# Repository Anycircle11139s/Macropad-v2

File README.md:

# Macropad-v2
<br>
<Br>

I wanted to make a second version of my macropad because I was confident, that with my improved skills, I could cook up something better. I spent a long time creating this, and I'm really proud of what I made. I just started by brainstorming what I wanted in my hackpad, and I searched up cool features to add, eventually ending with me designing a macropad and case with these items:
- Joystick
- 2 sliders
- 2 oleds
- buzzer
- Haptics
- rotary encoder
- cool cad case
- 12 switches
- Trackball
- hand gesture sensor
- bluetooth

<BR>
<br>

<BR>
<br>

<br>

<br>

BOM:
<Br>

|Name                |Purpose                               |Quantity|Total Cost (USD)|Link                                                                                                                                                                                                                                                                                                                                                                                                                                                                                                                                                                                                                                                                                                                                                                                   |Distributor|
|--------------------|--------------------------------------|--------|----------------|---------------------------------------------------------------------------------------------------------------------------------------------------------------------------------------------------------------------------------------------------------------------------------------------------------------------------------------------------------------------------------------------------------------------------------------------------------------------------------------------------------------------------------------------------------------------------------------------------------------------------------------------------------------------------------------------------------------------------------------------------------------------------------------|-----------|
|Case                |the case bruh                         |1       |6.50            |                                                                                                                                                                                                                                                                                                                                                                                                                                                                                                                                                                                                                                                                                                                                                                                       |Printing legion|
|PCB                 |the pcb ;(                            |1       |21.00           |                                                                                                                                                                                                                                                                                                                                                                                                                                                                                                                                                                                                                                                                                                                                                                                       |JLCPCB     |
|lipo battery        |battery                               |1       |0.99            |https://www.aliexpress.com/item/1005011541940994.html?spm=a2g0o.productlist.main.1.78703235cGbLFG&algo_pvid=9ee0d42c-760b-4657-89e7-614624b4ca0b&algo_exp_id=9ee0d42c-760b-4657-89e7-614624b4ca0b-0&pdp_ext_f=%7B%22order%22%3A%2291%22%2C%22eval%22%3A%221%22%2C%22fromPage%22%3A%22search%22%7D&pdp_npi=6%40dis%21USD%2113.94%210.99%21%21%2194.86%216.74%21%4021030a6217771838339585944e4a30%2112000055868825938%21sea%21AU%217402515296%21X%211%210%21n_tag%3A-29911%3Bd%3Aef1e07f3%3Bm03_new_user%3A-29895%3BpisId%3A5000000204047332&curPageLogUid=xRO33uo723qw&utparam-url=scene%3Asearch%7Cquery_from%3A%7Cx_object_id%3A1005011541940994%7C_p_origin_prod%3A                                                                                                                  |ali express|
|joystick            |for joy and happiness and sticks      |2       |0.99            |https://www.aliexpress.com/item/1005006375332797.html?spm=a2g0o.productlist.main.15.5f8999mT99mTyR&algo_pvid=a52f8a2f-d575-4ad3-bee8-e1a1bf34a230&algo_exp_id=a52f8a2f-d575-4ad3-bee8-e1a1bf34a230-12&pdp_ext_f=%7B%22order%22%3A%221642%22%2C%22eval%22%3A%221%22%2C%22fromPage%22%3A%22search%22%7D&pdp_npi=6%40dis%21USD%215.56%210.99%21%21%2137.82%216.70%21%40210328db17771815335367219ee95e%2112000037014017250%21sea%21AU%217402515296%21X%211%210%21n_tag%3A-29911%3Bd%3Aef1e07f3%3Bm03_new_user%3A-29895%3BpisId%3A5000000204047332&curPageLogUid=3UEUdfj2OnjF&utparam-url=scene%3Asearch%7Cquery_from%3A%7Cx_object_id%3A1005006375332797%7C_p_origin_prod%3A                                                                                                               |ali express|
|slide pot           |sliders                               |2       |5.70            |https://www.aliexpress.com/item/1005008713345793.html?spm=a2g0o.productlist.main.2.60983Pyu3PyuP1&algo_pvid=b0022195-0b79-4524-aa97-ece731d8ad54&algo_exp_id=b0022195-0b79-4524-aa97-ece731d8ad54-1&pdp_ext_f=%7B%22order%22%3A%22681%22%2C%22eval%22%3A%221%22%2C%22fromPage%22%3A%22search%22%7D&pdp_npi=6%40dis%21USD%212.66%210.99%21%21%2118.09%216.73%21%402101ee6617771813279241737e662c%2112000046545295127%21sea%21AU%217402515296%21X%211%210%21n_tag%3A-29911%3Bd%3Aef1e07f3%3Bm03_new_user%3A-29895%3BpisId%3A5000000204047332&curPageLogUid=FXsnTpFwKMfe&utparam-url=scene%3Asearch%7Cquery_from%3A%7Cx_object_id%3A1005008713345793%7C_p_origin_prod%3A                                                                                                                  |ali express|
|haptic motor        |haptics                               |1       |1.82            |https://www.aliexpress.com/item/1005007159921749.html?spm=a2g0o.productlist.main.28.3a4fJNUzJNUzMS&algo_pvid=4b836aab-1aa2-46ce-8623-293a19b2cf31&algo_exp_id=4b836aab-1aa2-46ce-8623-293a19b2cf31-25&pdp_ext_f=%7B%22order%22%3A%22448%22%2C%22eval%22%3A%221%22%2C%22fromPage%22%3A%22search%22%7D&pdp_npi=6%40dis%21USD%211.79%210.99%21%21%211.79%210.99%21%402101dedf17771845479125689ef0ce%2112000055867640789%21sea%21AU%217402515296%21X%211%210%21n_tag%3A-29911%3Bd%3Aef1e07f3%3Bm03_new_user%3A-29895%3BpisId%3A5000000204047332&curPageLogUid=zrmwNkYZNhYB&utparam-url=scene%3Asearch%7Cquery_from%3A%7Cx_object_id%3A1005007159921749%7C_p_origin_prod%3A                                                                                                                 |ali express|
|trackball           |trackball                             |1       |3.70            |https://www.aliexpress.com/item/1005008126890596.html?src=google#nav-description                                                                                                                                                                                                                                                                                                                                                                                                                                                                                                                                                                                                                                                                                                       |ali express|
|tof sensor          |hand gestures                         |1       |1.54            |https://www.aliexpress.com/item/1005006864257651.html?spm=a2g0o.productlist.main.4.351chWtAhWtATp&aem_p4p_detail=202604242032431273050239645690001515361&algo_pvid=fb4b63c4-da61-480d-ab27-ada5671d1d0b&algo_exp_id=fb4b63c4-da61-480d-ab27-ada5671d1d0b-3&pdp_ext_f=%7B%22order%22%3A%22413%22%2C%22eval%22%3A%221%22%2C%22fromPage%22%3A%22search%22%7D&pdp_npi=6%40dis%21USD%2135.42%211.54%21%21%21240.96%2110.50%21%402103212b17770879639204117eb09f%2112000038554217788%21sea%21AU%217402515296%21X%211%210%21n_tag%3A-29911%3Bd%3Aef1e07f3%3Bm03_new_user%3A-29895%3BpisId%3A5000000204047332&curPageLogUid=MrmJQzMoGh3t&utparam-url=scene%3Asearch%7Cquery_from%3A%7Cx_object_id%3A1005006864257651%7C_p_origin_prod%3A&search_p4p_id=202604242032431273050239645690001515361_1|ali express|
|DRV2605LDGS         |haptics driver                        |1       |3.60            |https://www.aliexpress.com/item/1005009975089617.html?spm=a2g0o.productlist.main.3.40e462b9pzbfZW&algo_pvid=4767538b-1ca2-4c58-b87e-f0fffccde297&algo_exp_id=4767538b-1ca2-4c58-b87e-f0fffccde297-2&pdp_ext_f=%7B%22order%22%3A%2229%22%2C%22eval%22%3A%221%22%2C%22fromPage%22%3A%22search%22%7D&pdp_npi=6%40dis%21USD%214.00%213.60%21%21%214.00%213.60%21%40210328db17770790445696115ee946%2112000050735812690%21sea%21AU%217402515296%21X%211%210%21n_tag%3A-29911%3Bd%3Aef1e07f3%3Bm03_new_user%3A-29895&curPageLogUid=5ZwdNp8fQ9ho&utparam-url=scene%3Asearch%7Cquery_from%3A%7Cx_object_id%3A1005009975089617%7C_p_origin_prod%3A                                                                                                                                               |ali express|
|24LC256             |for extra memory                      |1       |3.67            |https://www.aliexpress.com/item/1005007758875314.html?spm=a2g0o.productlist.main.1.1ba8766eaBLlFp&algo_pvid=40afdb6a-6caa-4c82-9273-4b09ec377997&algo_exp_id=40afdb6a-6caa-4c82-9273-4b09ec377997-0&pdp_ext_f=%7B%22order%22%3A%2272%22%2C%22eval%22%3A%221%22%2C%22fromPage%22%3A%22search%22%7D&pdp_npi=6%40dis%21USD%211.15%211.15%21%21%217.80%217.80%21%402103126e17771071385293001e5951%2112000042106872103%21sea%21AU%217402515296%21X%211%210%21n_tag%3A-29911%3Bd%3Aef1e07f3%3Bm03_new_user%3A-29895&curPageLogUid=d8mRjZi8dGUy&utparam-url=scene%3Asearch%7Cquery_from%3A%7Cx_object_id%3A1005007758875314%7C_p_origin_prod%3A                                                                                                                                               |Ali express|
|I2C channel switcher|so I can run I2C with that many things|1       |2.94            |https://www.aliexpress.com/item/4000321651168.html?spm=a2g0o.productlist.main.4.7c875bbcNb0561&aem_p4p_detail=202604241744053201409699771840001428483&algo_pvid=184a297b-85c3-4432-947e-2ee3c0819f25&algo_exp_id=184a297b-85c3-4432-947e-2ee3c0819f25-3&pdp_ext_f=%7B%22order%22%3A%2256%22%2C%22eval%22%3A%221%22%2C%22fromPage%22%3A%22search%22%7D&pdp_npi=6%40dis%21USD%213.27%212.94%21%21%213.27%212.94%21%402101c59117770778453443477e32c9%2110000001317042990%21sea%21AU%217402515296%21X%211%210%21n_tag%3A-29911%3Bd%3Aef1e07f3%3Bm03_new_user%3A-29895&curPageLogUid=kvqc1Zd7ka2i&utparam-url=scene%3Asearch%7Cquery_from%3A%7Cx_object_id%3A4000321651168%7C_p_origin_prod%3A&search_p4p_id=202604241744053201409699771840001428483_1                                      |ali express|
|ads1115             |for the sliders and joystick          |1       |3.27            |https://www.aliexpress.com/item/4000116831589.html?spm=a2g0o.productlist.main.4.e4367170pqiJeh&algo_pvid=54b18df7-b4a7-4482-b792-d480d9cb0b9a&aem_p4p_detail=202604241740286255615724926120001424947&algo_exp_id=54b18df7-b4a7-4482-b792-d480d9cb0b9a-3&pdp_ext_f=%7B%22order%22%3A%22359%22%2C%22eval%22%3A%221%22%2C%22fromPage%22%3A%22search%22%7D&pdp_npi=6%40dis%21USD%213.63%213.27%21%21%213.63%213.27%21%402101eee917770776282871616e7bde%2112000031353532263%21sea%21AU%217402515296%21X%211%210%21n_tag%3A-29911%3Bd%3Aef1e07f3%3Bm03_new_user%3A-29895&curPageLogUid=sNNybvIUvGwU&utparam-url=scene%3Asearch%7Cquery_from%3A%7Cx_object_id%3A4000116831589%7C_p_origin_prod%3A&search_p4p_id=202604241740286255615724926120001424947_1                                     |ali express|
|io expander         |more pins                             |1       |3.83            |https://www.aliexpress.com/item/1005006123427728.html?spm=a2g0o.productlist.main.4.7a5eTuUZTuUZsd&aem_p4p_detail=202604241737018054978755135470001446003&algo_pvid=2935dea7-c566-4d6d-8b4a-c8921f2ee585&algo_exp_id=2935dea7-c566-4d6d-8b4a-c8921f2ee585-3&pdp_ext_f=%7B%22order%22%3A%2213%22%2C%22eval%22%3A%221%22%2C%22fromPage%22%3A%22search%22%7D&pdp_npi=6%40dis%21USD%213.83%213.83%21%21%2126.05%2126.05%21%4021033d1217770774214177052eb5ec%2112000035859022158%21sea%21AU%217402515296%21X%211%210%21n_tag%3A-29911%3Bd%3Aef1e07f3%3Bm03_new_user%3A-29895&curPageLogUid=0Dl325w86X0G&utparam-url=scene%3Asearch%7Cquery_from%3A%7Cx_object_id%3A1005006123427728%7C_p_origin_prod%3A&search_p4p_id=202604241737018054978755135470001446003_1                              |ali express|
|headers             |headers                               |1       |1.23            |https://www.aliexpress.com/item/1005011980100152.html?spm=a2g0o.productlist.main.1.781emfhzmfhz9d&algo_pvid=7a2bb4b6-e92c-4a5b-a89d-71b8a1096902&algo_exp_id=7a2bb4b6-e92c-4a5b-a89d-71b8a1096902-0&pdp_ext_f=%7B%22order%22%3A%2218%22%2C%22eval%22%3A%221%22%2C%22fromPage%22%3A%22search%22%7D&pdp_npi=6%40dis%21USD%211.23%211.20%21%21%211.23%211.20%21%40210328d417770772722275687ecccc%2112000057423435803%21sea%21AU%217402515296%21X%211%210%21n_tag%3A-29911%3Bd%3Aef1e07f3%3Bm03_new_user%3A-29895&curPageLogUid=sG8mgvOClCPu&utparam-url=scene%3Asearch%7Cquery_from%3A%7Cx_object_id%3A1005011980100152%7C_p_origin_prod%3A                                                                                                                                               |ali express|
|buzzer              |buzzing                               |2       |5.50            |https://www.aliexpress.com/item/1005007760117171.html?spm=a2g0o.productlist.main.3.6030mV5emV5e3L&algo_pvid=eef0c9b7-e91c-4ed5-b4f4-4c7a828aafc4&algo_exp_id=eef0c9b7-e91c-4ed5-b4f4-4c7a828aafc4-2&pdp_ext_f=%7B%22order%22%3A%2249%22%2C%22eval%22%3A%221%22%2C%22fromPage%22%3A%22search%22%7D&pdp_npi=6%40dis%21USD%212.87%210.99%21%21%2119.49%216.70%21%402103129f17771804952892675e59d3%2112000042136775304%21sea%21AU%217402515296%21X%211%210%21n_tag%3A-29911%3Bd%3Aef1e07f3%3Bm03_new_user%3A-29895%3BpisId%3A5000000204047332&curPageLogUid=3fwWn3qz4T5N&utparam-url=scene%3Asearch%7Cquery_from%3A%7Cx_object_id%3A1005007760117171%7C_p_origin_prod%3A                                                                                                                   |ali express|
|rotary encoder      |to rotary encode                      |1       |1.29            |https://www.aliexpress.com/item/1005007644083514.html?spm=a2g0o.productlist.main.1.7b187465T0x8DI&algo_pvid=dd42beb6-a89c-4e9a-822a-aee0d3bb8655&algo_exp_id=dd42beb6-a89c-4e9a-822a-aee0d3bb8655-0&pdp_ext_f=%7B%22order%22%3A%222833%22%2C%22spu_best_type%22%3A%22price%22%2C%22eval%22%3A%221%22%2C%22fromPage%22%3A%22search%22%7D&pdp_npi=6%40dis%21USD%211.17%210.99%21%21%211.17%210.99%21%402101ee6617770766332183942e6637%2112000041630839415%21sea%21AU%217402515296%21X%211%210%21n_tag%3A-29911%3Bd%3Aef1e07f3%3Bm03_new_user%3A-29895%3BpisId%3A5000000204047332&curPageLogUid=TOJyxlb254yR&utparam-url=scene%3Asearch%7Cquery_from%3A%7Cx_object_id%3A1005007644083514%7C_p_origin_prod%3A                                                                              |ali express|
|150r resistors      |resisting                             |1       |1.79            |https://www.aliexpress.com/item/1005011779163101.html?spm=a2g0o.productlist.main.1.165bKPGbKPGb9c&algo_pvid=6a77e362-f1ba-4f46-bcf4-28d82e9b39d5&algo_exp_id=6a77e362-f1ba-4f46-bcf4-28d82e9b39d5-0&pdp_ext_f=%7B%22order%22%3A%22384%22%2C%22eval%22%3A%221%22%2C%22fromPage%22%3A%22search%22%7D&pdp_npi=6%40dis%21USD%211.74%211.74%21%21%2111.86%2111.86%21%4021030a4b17770764663682662e7f12%2112000056534710403%21sea%21AU%217402515296%21X%211%210%21n_tag%3A-29911%3Bd%3Aef1e07f3%3Bm03_new_user%3A-29895&curPageLogUid=lPvCdQ65XX0q&utparam-url=scene%3Asearch%7Cquery_from%3A%7Cx_object_id%3A1005011779163101%7C_p_origin_prod%3A                                                                                                                                            |ali express|
|100r resistors      |resisting                             |1       |1.79            |https://www.aliexpress.com/item/1005011779163101.html?spm=a2g0o.productlist.main.1.165bKPGbKPGb9c&algo_pvid=6a77e362-f1ba-4f46-bcf4-28d82e9b39d5&algo_exp_id=6a77e362-f1ba-4f46-bcf4-28d82e9b39d5-0&pdp_ext_f=%7B%22order%22%3A%22384%22%2C%22eval%22%3A%221%22%2C%22fromPage%22%3A%22search%22%7D&pdp_npi=6%40dis%21USD%211.74%211.74%21%21%2111.86%2111.86%21%4021030a4b17770764663682662e7f12%2112000056534710403%21sea%21AU%217402515296%21X%211%210%21n_tag%3A-29911%3Bd%3Aef1e07f3%3Bm03_new_user%3A-29895&curPageLogUid=lPvCdQ65XX0q&utparam-url=scene%3Asearch%7Cquery_from%3A%7Cx_object_id%3A1005011779163101%7C_p_origin_prod%3A                                                                                                                                            |ali express|
|2.2k resistors      |resisting                             |1       |1.79            |https://www.aliexpress.com/item/1005011779163101.html?spm=a2g0o.productlist.main.1.165bKPGbKPGb9c&algo_pvid=6a77e362-f1ba-4f46-bcf4-28d82e9b39d5&algo_exp_id=6a77e362-f1ba-4f46-bcf4-28d82e9b39d5-0&pdp_ext_f=%7B%22order%22%3A%22384%22%2C%22eval%22%3A%221%22%2C%22fromPage%22%3A%22search%22%7D&pdp_npi=6%40dis%21USD%211.74%211.74%21%21%2111.86%2111.86%21%4021030a4b17770764663682662e7f12%2112000056534710403%21sea%21AU%217402515296%21X%211%210%21n_tag%3A-29911%3Bd%3Aef1e07f3%3Bm03_new_user%3A-29895&curPageLogUid=lPvCdQ65XX0q&utparam-url=scene%3Asearch%7Cquery_from%3A%7Cx_object_id%3A1005011779163101%7C_p_origin_prod%3A                                                                                                                                            |ali exress |
|m4 screws           |to mount PCB                          |1       |1.31            |https://www.aliexpress.com/item/1005005879037174.html?mp=1&pdp_npi=6@dis!USD!USD+1.11!USD+1.09!!USD+1.09!!!@2101e2b417770758950625236e1519!12000034679037238!ct!AU!7402515296!!1!0!                                                                                                                                                                                                                                                                                                                                                                                                                                                                                                                                                                                                    |ali express|
|m2 screws           |to hold case together                 |1       |1.58            |https://www.aliexpress.com/item/1005005879037174.html?mp=1&pdp_npi=6@dis!USD!USD+1.11!USD+1.09!!USD+1.09!!!@2101e2b417770758950625236e1519!12000034679037238!ct!AU!7402515296!!1!0!                                                                                                                                                                                                                                                                                                                                                                                                                                                                                                                                                                                                    |ali express|
|Keycaps             |to cover switches                     |1       |4.20            |https://www.aliexpress.com/item/1005008678389468.html?mp=1&pdp_npi=6@dis!USD!USD+4.23!USD+4.23!!USD+4.23!!!@2101e2b417770757558731632e1519!12000046204757642!ct!AU!7402515296!!1!0!                                                                                                                                                                                                                                                                                                                                                                                                                                                                                                                                                                                                    |ali express|
|Diodes              |for switch matrix                     |1       |2.83            |https://www.aliexpress.com/item/1005007606166130.html?mp=1&pdp_npi=6@dis!USD!USD+2.83!USD+2.83!!USD+2.74!!!@2101e2b417770757117688866e1519!12000045210201538!ct!AU!7402515296!!1!0!                                                                                                                                                                                                                                                                                                                                                                                                                                                                                                                                                                                                    |Ali express|
|Oleds               |2 oleds                               |2       |7.00            |https://www.aliexpress.com/item/1005006636072295.html?mp=1&pdp_npi=6@dis!USD!USD+3.50!USD+2.30!!USD+2.28!!!@2101e2b417770756812038247e1519!12000037978554141!ct!AU!7402515296!!1!0!                                                                                                                                                                                                                                                                                                                                                                                                                                                                                                                                                                                                    |ali express|
|Switches            |buttons                               |1       |8.40            |https://www.aliexpress.com/item/1005006425450443.html?mp=1&pdp_npi=6@dis!USD!USD+8.40!USD+0.99!!USD+0.99!!!@2101e2b417770755354165492e1519!12000037120671470!ct!AU!7402515296!!1!0!                                                                                                                                                                                                                                                                                                                                                                                                                                                                                                                                                                                                    |ali express|
|rgb leds            |backlighting                          |1       |3.23            |https://www.aliexpress.com/item/1005005340818659.html?mp=1&pdp_npi=6@dis!USD!USD+3.80!USD+3.23!!USD+3.23!!!@2101e2b417770753745202285e1519!12000032670306832!ct!AU!7402515296!!1!0!                                                                                                                                                                                                                                                                                                                                                                                                                                                                                                                                                                                                    |Ali express|
|Capacitors          |to capacitate                         |1       |1.00            |https://www.aliexpress.com/item/1005010764953411.html?spm=a2g0o.productlist.main.1.e6475d075FSaEj&algo_pvid=772381fe-7654-43a5-9bd3-7f88d16dd3aa&algo_exp_id=772381fe-7654-43a5-9bd3-7f88d16dd3aa-0&pdp_ext_f=%7B%22order%22%3A%22160%22%2C%22eval%22%3A%221%22%2C%22fromPage%22%3A%22search%22%7D&pdp_npi=6%40dis%21USD%216.40%210.99%21%21%2143.56%216.76%21%40210319b717770753721454899e46bd%2112000053431436229%21sea%21AU%217402515296%21X%211%210%21n_tag%3A-29911%3Bd%3Aef1e07f3%3Bm03_new_user%3A-29895%3BpisId%3A5000000204047332&curPageLogUid=IRwD1Amro2MH&utparam-url=scene%3Asearch%7Cquery_from%3A%7Cx_object_id%3A1005010764953411%7C_p_origin_prod%3A                                                                                                                  |ali express|
|Xiao esp32 s3       |microcontroller                       |1       |11.00           |https://www.aliexpress.com/item/1005007870593864.html?spm=a2g0o.productlist.main.2.429f1518C9k5jO&algo_pvid=f75b72cf-3b9b-4d39-bf3e-6999bac9bbf1&algo_exp_id=f75b72cf-3b9b-4d39-bf3e-6999bac9bbf1-1&pdp_ext_f=%7B%22order%22%3A%2285%22%2C%22eval%22%3A%221%22%2C%22fromPage%22%3A%22search%22%7D&pdp_npi=6%40dis%21USD%210.26%210.19%21%21%210.26%210.19%21%4021030a6217771807664662117e4a39%2112000053238173498%21sea%21AU%217402515296%21X%211%210%21n_tag%3A-29911%3Bd%3Aef1e07f3%3Bm03_new_user%3A-29895&curPageLogUid=QZZSsXEuP658&utparam-url=scene%3Asearch%7Cquery_from%3A%7Cx_object_id%3A1005007870593864%7C_p_origin_prod%3A                                                                                                                                               |ali express|
|Total       |                       |113.50       |          |                                                                                                                                             ||

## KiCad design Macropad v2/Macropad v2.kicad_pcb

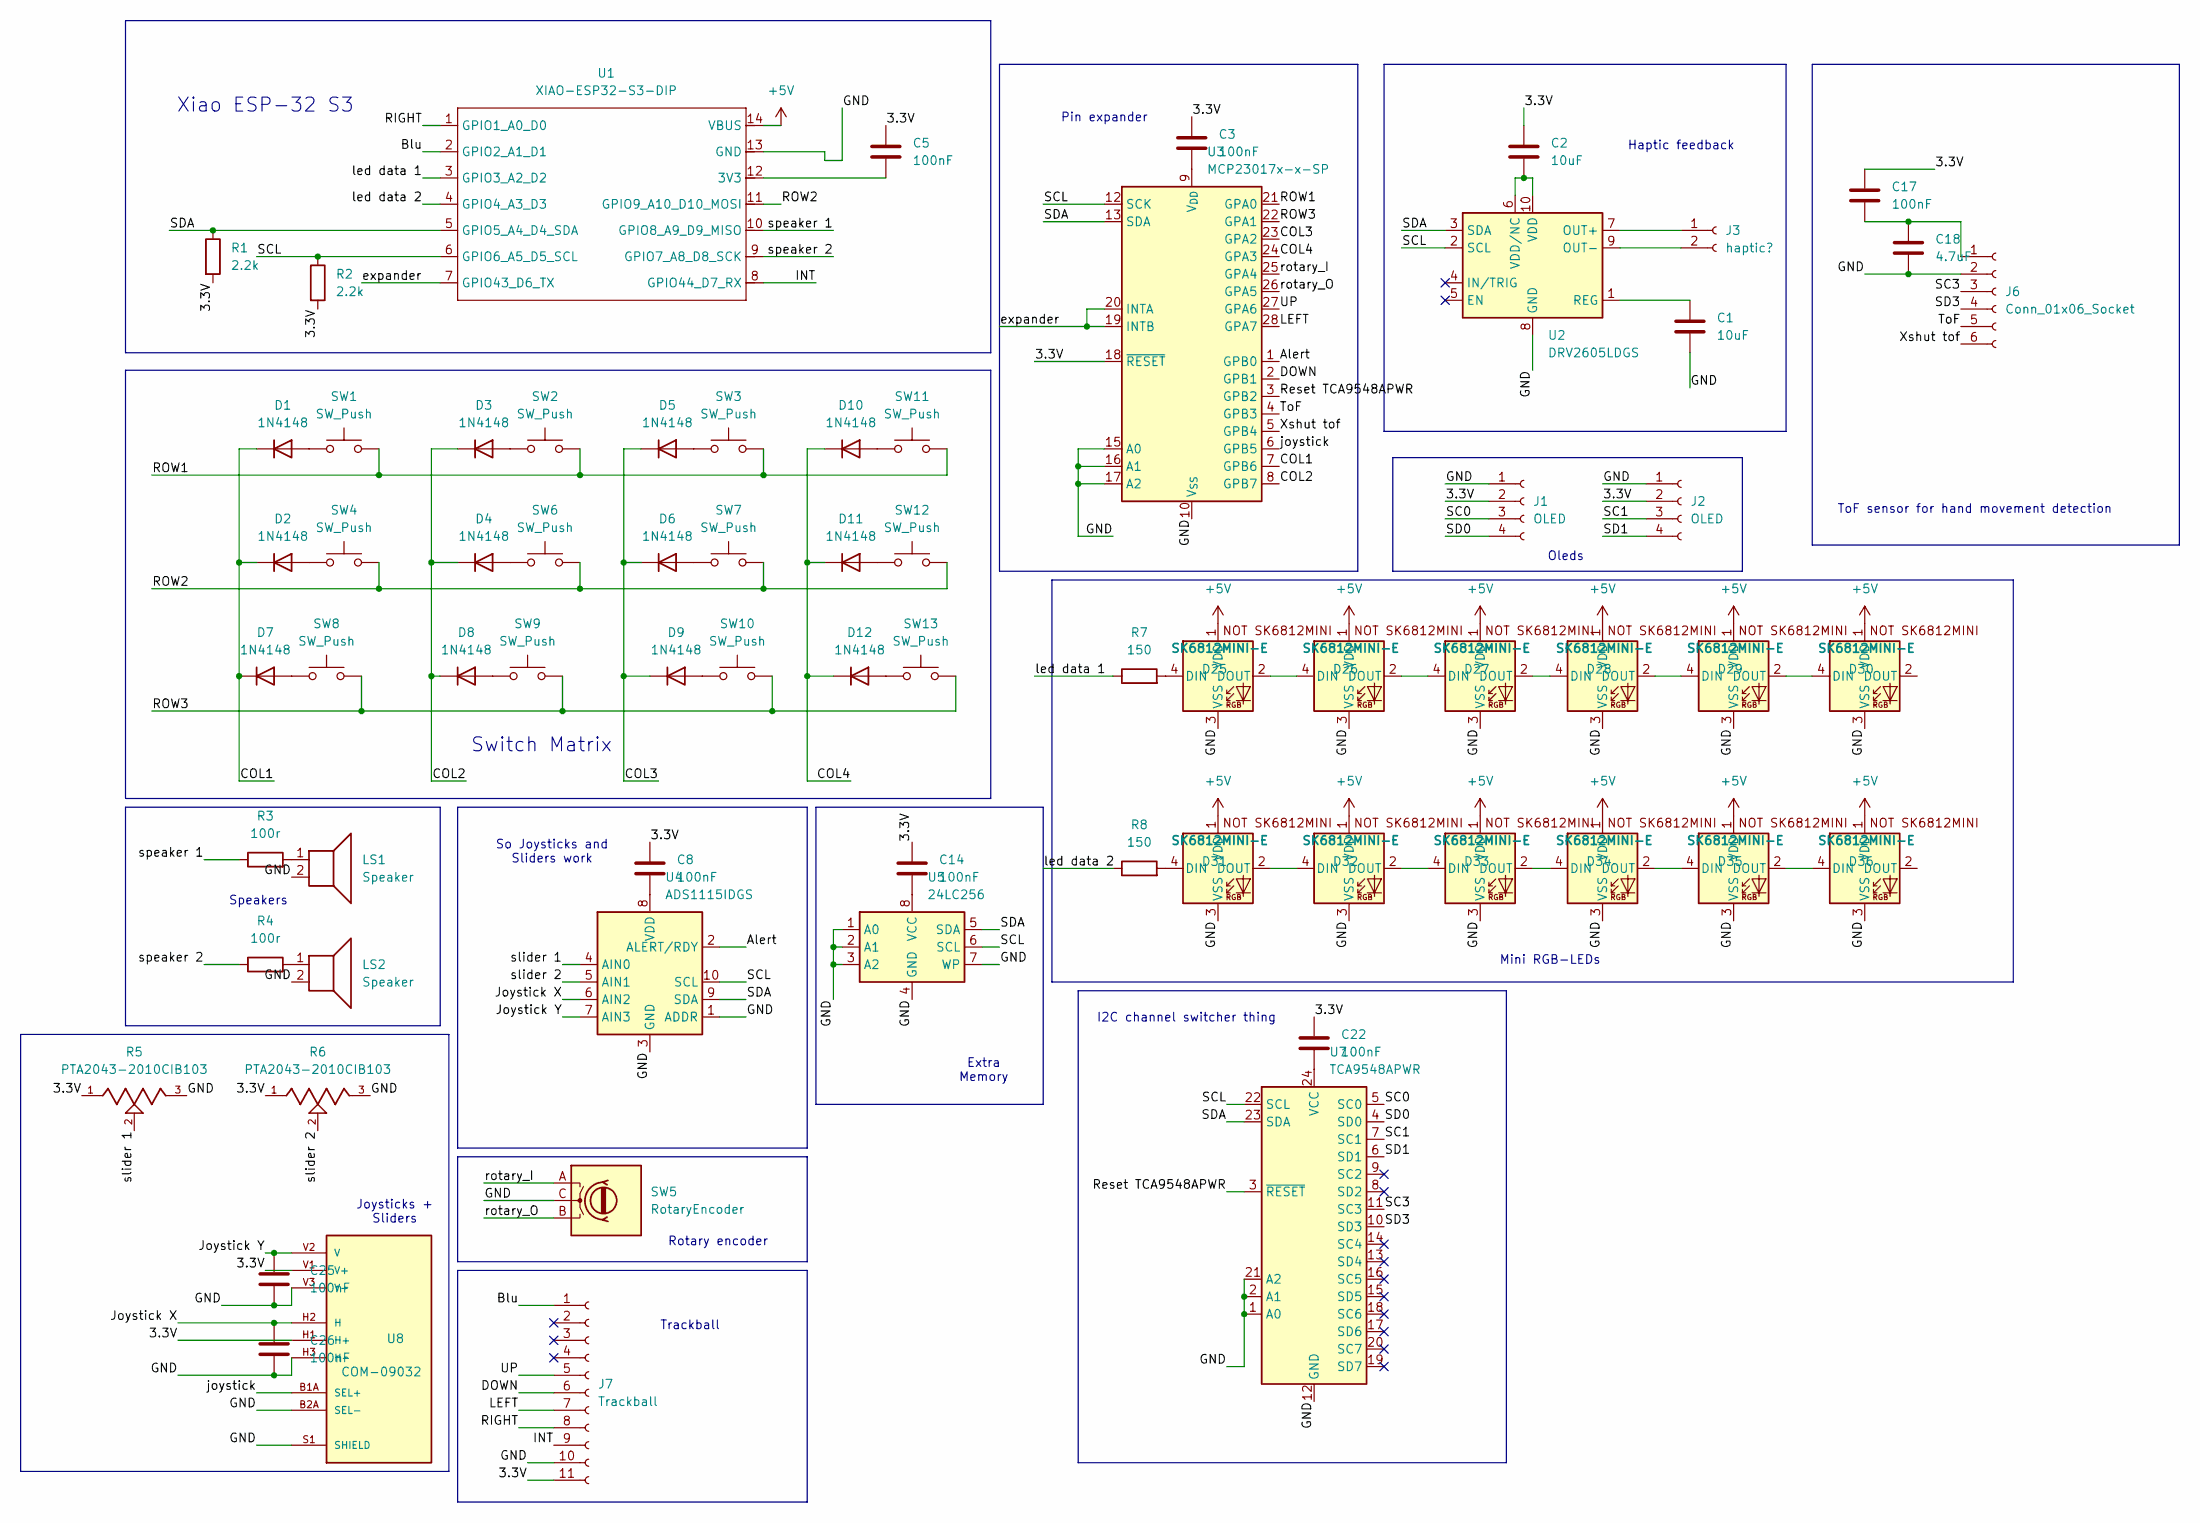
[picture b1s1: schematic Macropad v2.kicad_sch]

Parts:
C1, C2: 10uF; C_1206_3216Metric_Pad1.33x1.80mm_HandSolder
C3, C5, C8, C14, C17, C22, C25, C26: 100nF; C_1206_3216Metric_Pad1.33x1.80mm_HandSolder
C18: 4.7uF; C_1206_3216Metric_Pad1.33x1.80mm_HandSolder
D1, D2, D3, D4, D5, D6, D7, D8, D9, D10, D11, D12: 1N4148; D_DO-35_SOD27_P7.62mm_Horizontal
D25, D26, D27, D28, D29, D30, D31, D32, D33, D34, D35, D36: SK6812MINI-E; SK6812MINI-E Fixed
J1, J2: OLED; SSD1306-0.91-OLED-4pin-128x32
J3: haptic?; PinHeader_1x02_P2.54mm_Vertical
J6: Conn_01x06_Socket; PinHeader_1x06_P2.54mm_Vertical
J7: Trackball; PinHeader_1x11_P2.54mm_Vertical
LS1, LS2: Speaker; XDCR_CMI-1210-5-95T
R1, R2: 2.2k; R_0805_2012Metric_Pad1.20x1.40mm_HandSolder
R3, R4: 100r; R_0805_2012Metric_Pad1.20x1.40mm_HandSolder
R5, R6: PTA2043-2010CIB103; TRIM_PTA2043-2010CIB103; PARTREV 04/21
R7, R8: 150; R_0805_2012Metric_Pad1.20x1.40mm_HandSolder
SW1, SW2, SW3, SW4, SW6, SW7, SW8, SW9, SW10, SW11, SW12, SW13: SW_Push; SW_Cherry_MX_1.00u_PCB
SW5: RotaryEncoder; RotaryEncoder_Alps_EC11E-Switch_Vertical_H20mm
U1: XIAO-ESP32-S3-DIP
U2: DRV2605LDGS; TSSOP-10_3x3mm_P0.5mm
U3: MCP23017x-x-SP; DIP-28_W7.62mm
U4: ADS1115IDGS; TSSOP-10_3x3mm_P0.5mm
U5: 24LC256; DIP-8_W7.62mm
U7: TCA9548APWR; TSSOP-24_4.4x7.8mm_P0.65mm
U8: COM-09032; XDCR_COM-09032; PARTREV N/A

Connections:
+5V: D25.1 (VDD), D26.1 (VDD), D27.1 (VDD), D28.1 (VDD), D29.1 (VDD), D30.1 (VDD), D31.1 (VDD), D32.1 (VDD), D33.1 (VDD), D34.1 (VDD), D35.1 (VDD), D36.1 (VDD), U1.14 (VBUS)
/3.3V: C2.1, C3.1, C5.1, C8.1, C14.1, C17.1, C22.1, J1.2, J2.2, J7.11, R1.2, R2.2, R5.1, R6.1, U3.18 (~RESET), U8.H1 (H+), U8.V1 (V+)
/Alert: U3.1 (GPB0), U4.2 (ALERT/RDY)
/Blu: J7.1, U1.2 (GPIO2_A1_D1)
/COL1: D1.1 (K), D2.1 (K), D7.1 (K), U3.7 (GPB6)
/COL2: D3.1 (K), D4.1 (K), D8.1 (K), U3.8 (GPB7)
/COL3: D5.1 (K), D6.1 (K), D9.1 (K), U3.23 (GPA2)
/COL4: D10.1 (K), D11.1 (K), D12.1 (K), U3.24 (GPA3)
/DOWN: J7.6, U3.2 (GPB1)
/GND: C1.2, C18.2, C25.2, C26.2, D25.3 (VSS), D26.3 (VSS), D27.3 (VSS), D28.3 (VSS), D29.3 (VSS), D30.3 (VSS), D31.3 (VSS), D32.3 (VSS), D33.3 (VSS), D34.3 (VSS), D35.3 (VSS), D36.3 (VSS), J1.1, J2.1, J6.2, J7.10, LS1.2, LS2.2, R5.3, R6.3, SW5.C, U1.13 (GND), U2.8 (GND), U3.10 (V_{SS}), U3.15 (A0), U3.16 (A1), U3.17 (A2), U4.1 (ADDR), U4.3 (GND), U5.1 (A0), U5.2 (A1), U5.3 (A2), U5.4 (GND), U5.7 (WP), U7.1 (A0), U7.2 (A1), U7.12 (GND), U7.21 (A2), U8.B2A (SEL-), U8.H3 (H-), U8.S1 (SHIELD), U8.S2 (SHIELD), U8.S3 (SHIELD), U8.S4 (SHIELD), U8.V3 (V-)
/INT: J7.9, U1.8 (GPIO44_D7_RX)
/Joystick X: C26.1, U4.6 (AIN2), U8.H2 (H)
/Joystick Y: C25.1, U4.7 (AIN3), U8.V2 (V)
/LEFT: J7.7, U3.28 (GPA7)
/RIGHT: J7.8, U1.1 (GPIO1_A0_D0)
/ROW1: SW1.2, SW2.2, SW3.2, SW11.2, U3.21 (GPA0)
/ROW2: SW4.2, SW6.2, SW7.2, SW12.2, U1.11 (GPIO9_A10_D10_MOSI)
/ROW3: SW8.2, SW9.2, SW10.2, SW13.2, U3.22 (GPA1)
/Reset TCA9548APWR: U3.3 (GPB2), U7.3 (~RESET)
/SC0: J1.3, U7.5 (SC0)
/SC1: J2.3, U7.7 (SC1)
/SC3: J6.3, U7.11 (SC3)
/SCL: R2.1, U1.6 (GPIO6_A5_D5_SCL), U2.2 (SCL), U3.12 (SCK), U4.10 (SCL), U5.6 (SCL), U7.22 (SCL)
/SD0: J1.4, U7.4 (SD0)
/SD1: J2.4, U7.6 (SD1)
/SD3: J6.4, U7.10 (SD3)
/SDA: R1.1, U1.5 (GPIO5_A4_D4_SDA), U2.3 (SDA), U3.13 (SDA), U4.9 (SDA), U5.5 (SDA), U7.23 (SDA)
/ToF: J6.5, U3.4 (GPB3)
/UP: J7.5, U3.27 (GPA6)
/Xshut tof: J6.6, U3.5 (GPB4)
/expander: U1.7 (GPIO43_D6_TX), U3.19 (INTB), U3.20 (INTA)
/joystick: U3.6 (GPB5), U8.B1A (SEL+)
/led data 1: R7.1, U1.3 (GPIO3_A2_D2)
/led data 2: R8.1, U1.4 (GPIO4_A3_D3)
/rotary_I: SW5.A, U3.25 (GPA4)
/rotary_O: SW5.B, U3.26 (GPA5)
/slider 1: R5.2, U4.4 (AIN0)
/slider 2: R6.2, U4.5 (AIN1)
/speaker 1: R3.1, U1.10 (GPIO8_A9_D9_MISO)
/speaker 2: R4.1, U1.9 (GPIO7_A8_D8_SCK)
unnamed: D1.2 (A), SW1.1
unnamed: D2.2 (A), SW4.1
unnamed: D3.2 (A), SW2.1
unnamed: D4.2 (A), SW6.1
unnamed: D5.2 (A), SW3.1
unnamed: D6.2 (A), SW7.1
unnamed: D7.2 (A), SW8.1
unnamed: D8.2 (A), SW9.1
unnamed: D9.2 (A), SW10.1
unnamed: D10.2 (A), SW11.1
unnamed: D11.2 (A), SW12.1
unnamed: D12.2 (A), SW13.1
unnamed: D25.4 (DIN), R7.2
unnamed: D25.2 (DOUT), D26.4 (DIN)
unnamed: D26.2 (DOUT), D27.4 (DIN)
unnamed: D27.2 (DOUT), D28.4 (DIN)
unnamed: D28.2 (DOUT), D29.4 (DIN)
unnamed: D29.2 (DOUT), D30.4 (DIN)
unnamed: D31.4 (DIN), R8.2
unnamed: D31.2 (DOUT), D32.4 (DIN)
unnamed: D32.2 (DOUT), D33.4 (DIN)
unnamed: D33.2 (DOUT), D34.4 (DIN)
unnamed: D34.2 (DOUT), D35.4 (DIN)
unnamed: D35.2 (DOUT), D36.4 (DIN)
unnamed: J3.1, U2.7 (OUT+)
unnamed: J3.2, U2.9 (OUT-)
unnamed: C17.2, C18.1, J6.1
unnamed: LS1.1, R3.2
unnamed: LS2.1, R4.2
unnamed: C5.2, U1.12 (3V3)
unnamed: C1.1, U2.1 (REG)
unnamed: C2.2, U2.6 (VDD/NC), U2.10 (VDD)
unnamed: C3.2, U3.9 (V_{DD})
unnamed: C8.2, U4.8 (VDD)
unnamed: C14.2, U5.8 (VCC)
unnamed: C22.2, U7.24 (VCC)

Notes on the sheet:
Trackball
Rotary encoder
Switch Matrix
Xiao ESP-32 S3
So Joysticks and Sliders work
Mini RGB-LEDs
I2C channel switcher thing
Oleds
Extra Memory
ToF sensor for hand movement detection
Pin expander
Speakers
Joysticks + Sliders
Haptic feedback

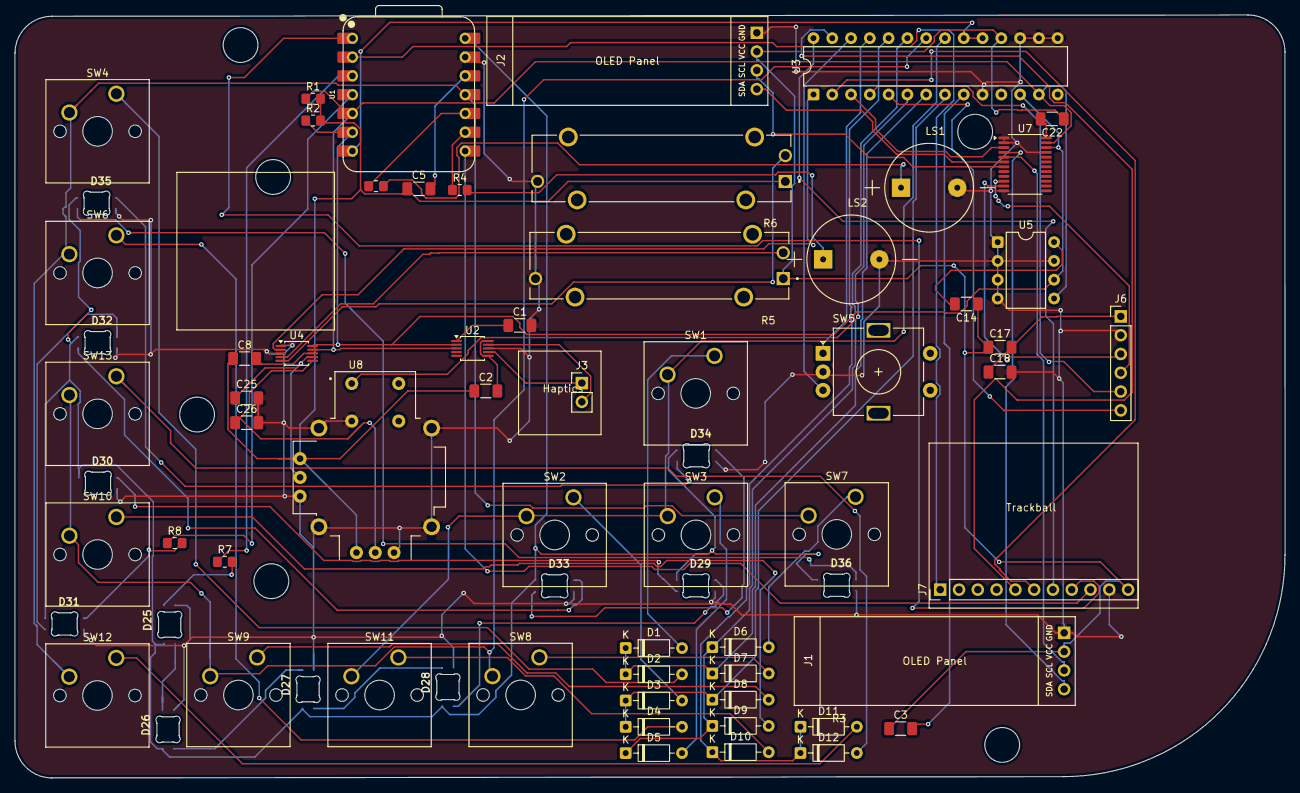
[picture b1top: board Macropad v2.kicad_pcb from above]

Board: 2 copper layers, 171.7 x 103.2 mm, 70 parts (0 on the bottom side), 76 nets.

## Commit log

2026-04-26 Update README with new images and BOM section
    Added additional images and BOM section to README.
